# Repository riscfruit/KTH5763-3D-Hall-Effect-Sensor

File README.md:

# KTH5763-3D-Hall-Effect-Sensor
Riscfruit CONNTEK KTH5763 3D Hall-Effect Sensor

### Gallery

### License
Copyright (c) 2026, Riscfruit Laboratory. This open source hardware is released under [CERN-OHL-S-2.0](LICENSE).

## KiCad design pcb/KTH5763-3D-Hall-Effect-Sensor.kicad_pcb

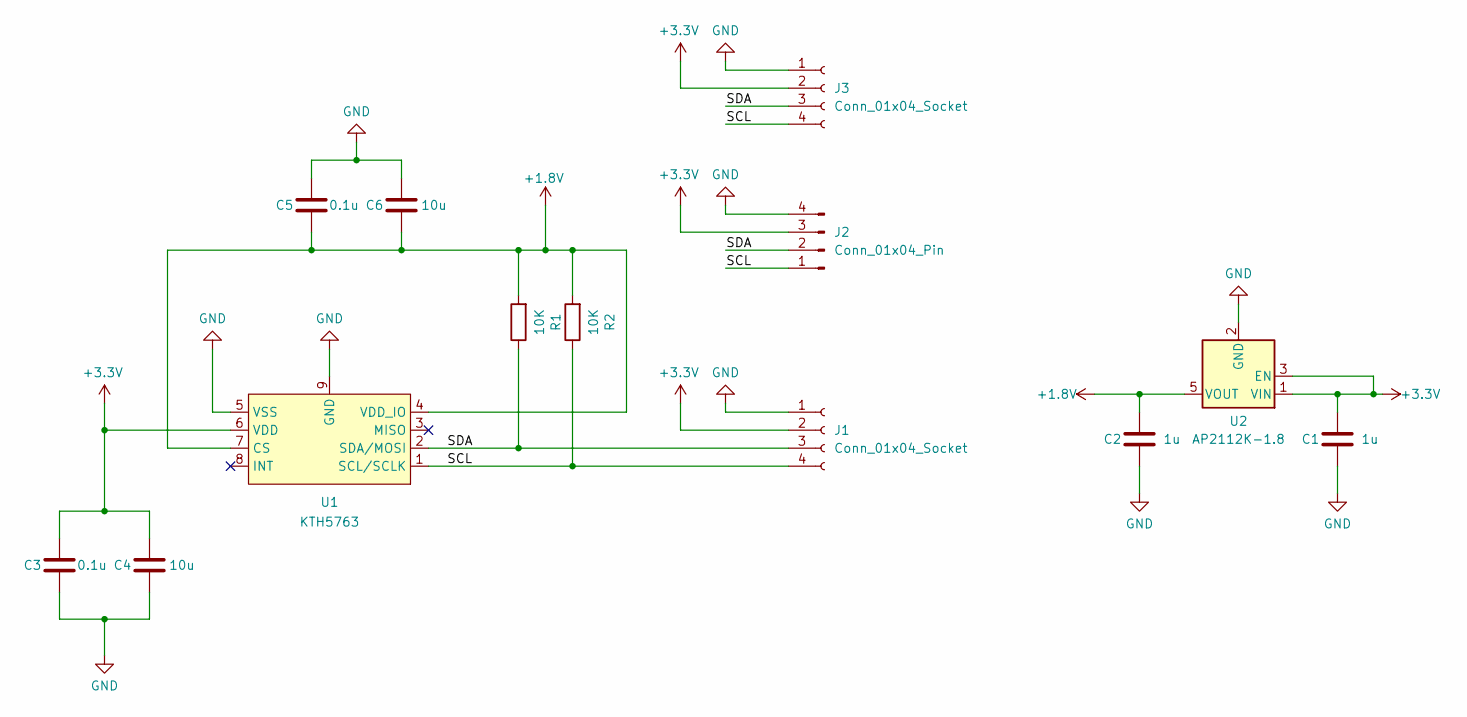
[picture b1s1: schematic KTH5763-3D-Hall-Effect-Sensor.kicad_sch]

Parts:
C1, C2: 1u; C_0402_1005Metric
C3, C5: 0.1u; C_0402_1005Metric
C4, C6: 10u; C_0402_1005Metric
J1, J3: Conn_01x04_Socket; JST_SH_SM04B-SRSS-TB_1x04-1MP_P1.00mm_Horizontal
J2: Conn_01x04_Pin; PinHeader_1x04_P2.54mm_Vertical
R1, R2: 10K; R_0402_1005Metric
U1: KTH5763; DFN-8_L2.5-W2.0-P0.50-TL-EP
U2: AP2112K-1.8; SOT-23-5

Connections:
+1.8V: C2.1, C5.2, C6.2, R1.2, R2.2, U1.4 (VDD_IO), U1.7 (CS), U2.5 (VOUT)
+3.3V: C1.1, C3.1, C4.1, J1.2, J2.3, J3.2, U1.6 (VDD), U2.1 (VIN), U2.3 (EN)
/SCL: J1.4, J2.1, J3.4, R2.1, U1.1 (SCL/SCLK)
/SDA: J1.3, J2.2, J3.3, R1.1, U1.2 (SDA/MOSI)
GND: C1.2, C2.2, C3.2, C4.2, C5.1, C6.1, J1.1, J2.4, J3.1, U1.5 (VSS), U1.9 (GND), U2.2 (GND)

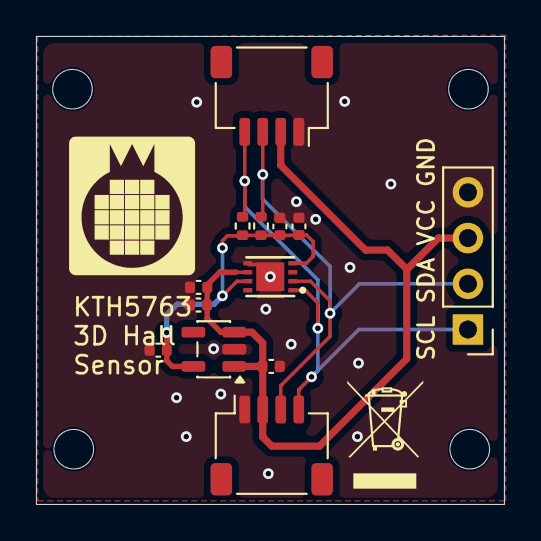
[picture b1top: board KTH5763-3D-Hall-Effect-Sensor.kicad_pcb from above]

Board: 2 copper layers, 26.0 x 26.0 mm, 17 parts (0 on the bottom side), 5 nets.

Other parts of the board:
H1, H1#2, H1#3, H1#4: MountingHole; MountingHole_2.2mm_M2

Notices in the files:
pcb/KTH5763-3D-Hall-Effect-Sensor.kicad_sch:
License: CERN OHL-S v2
